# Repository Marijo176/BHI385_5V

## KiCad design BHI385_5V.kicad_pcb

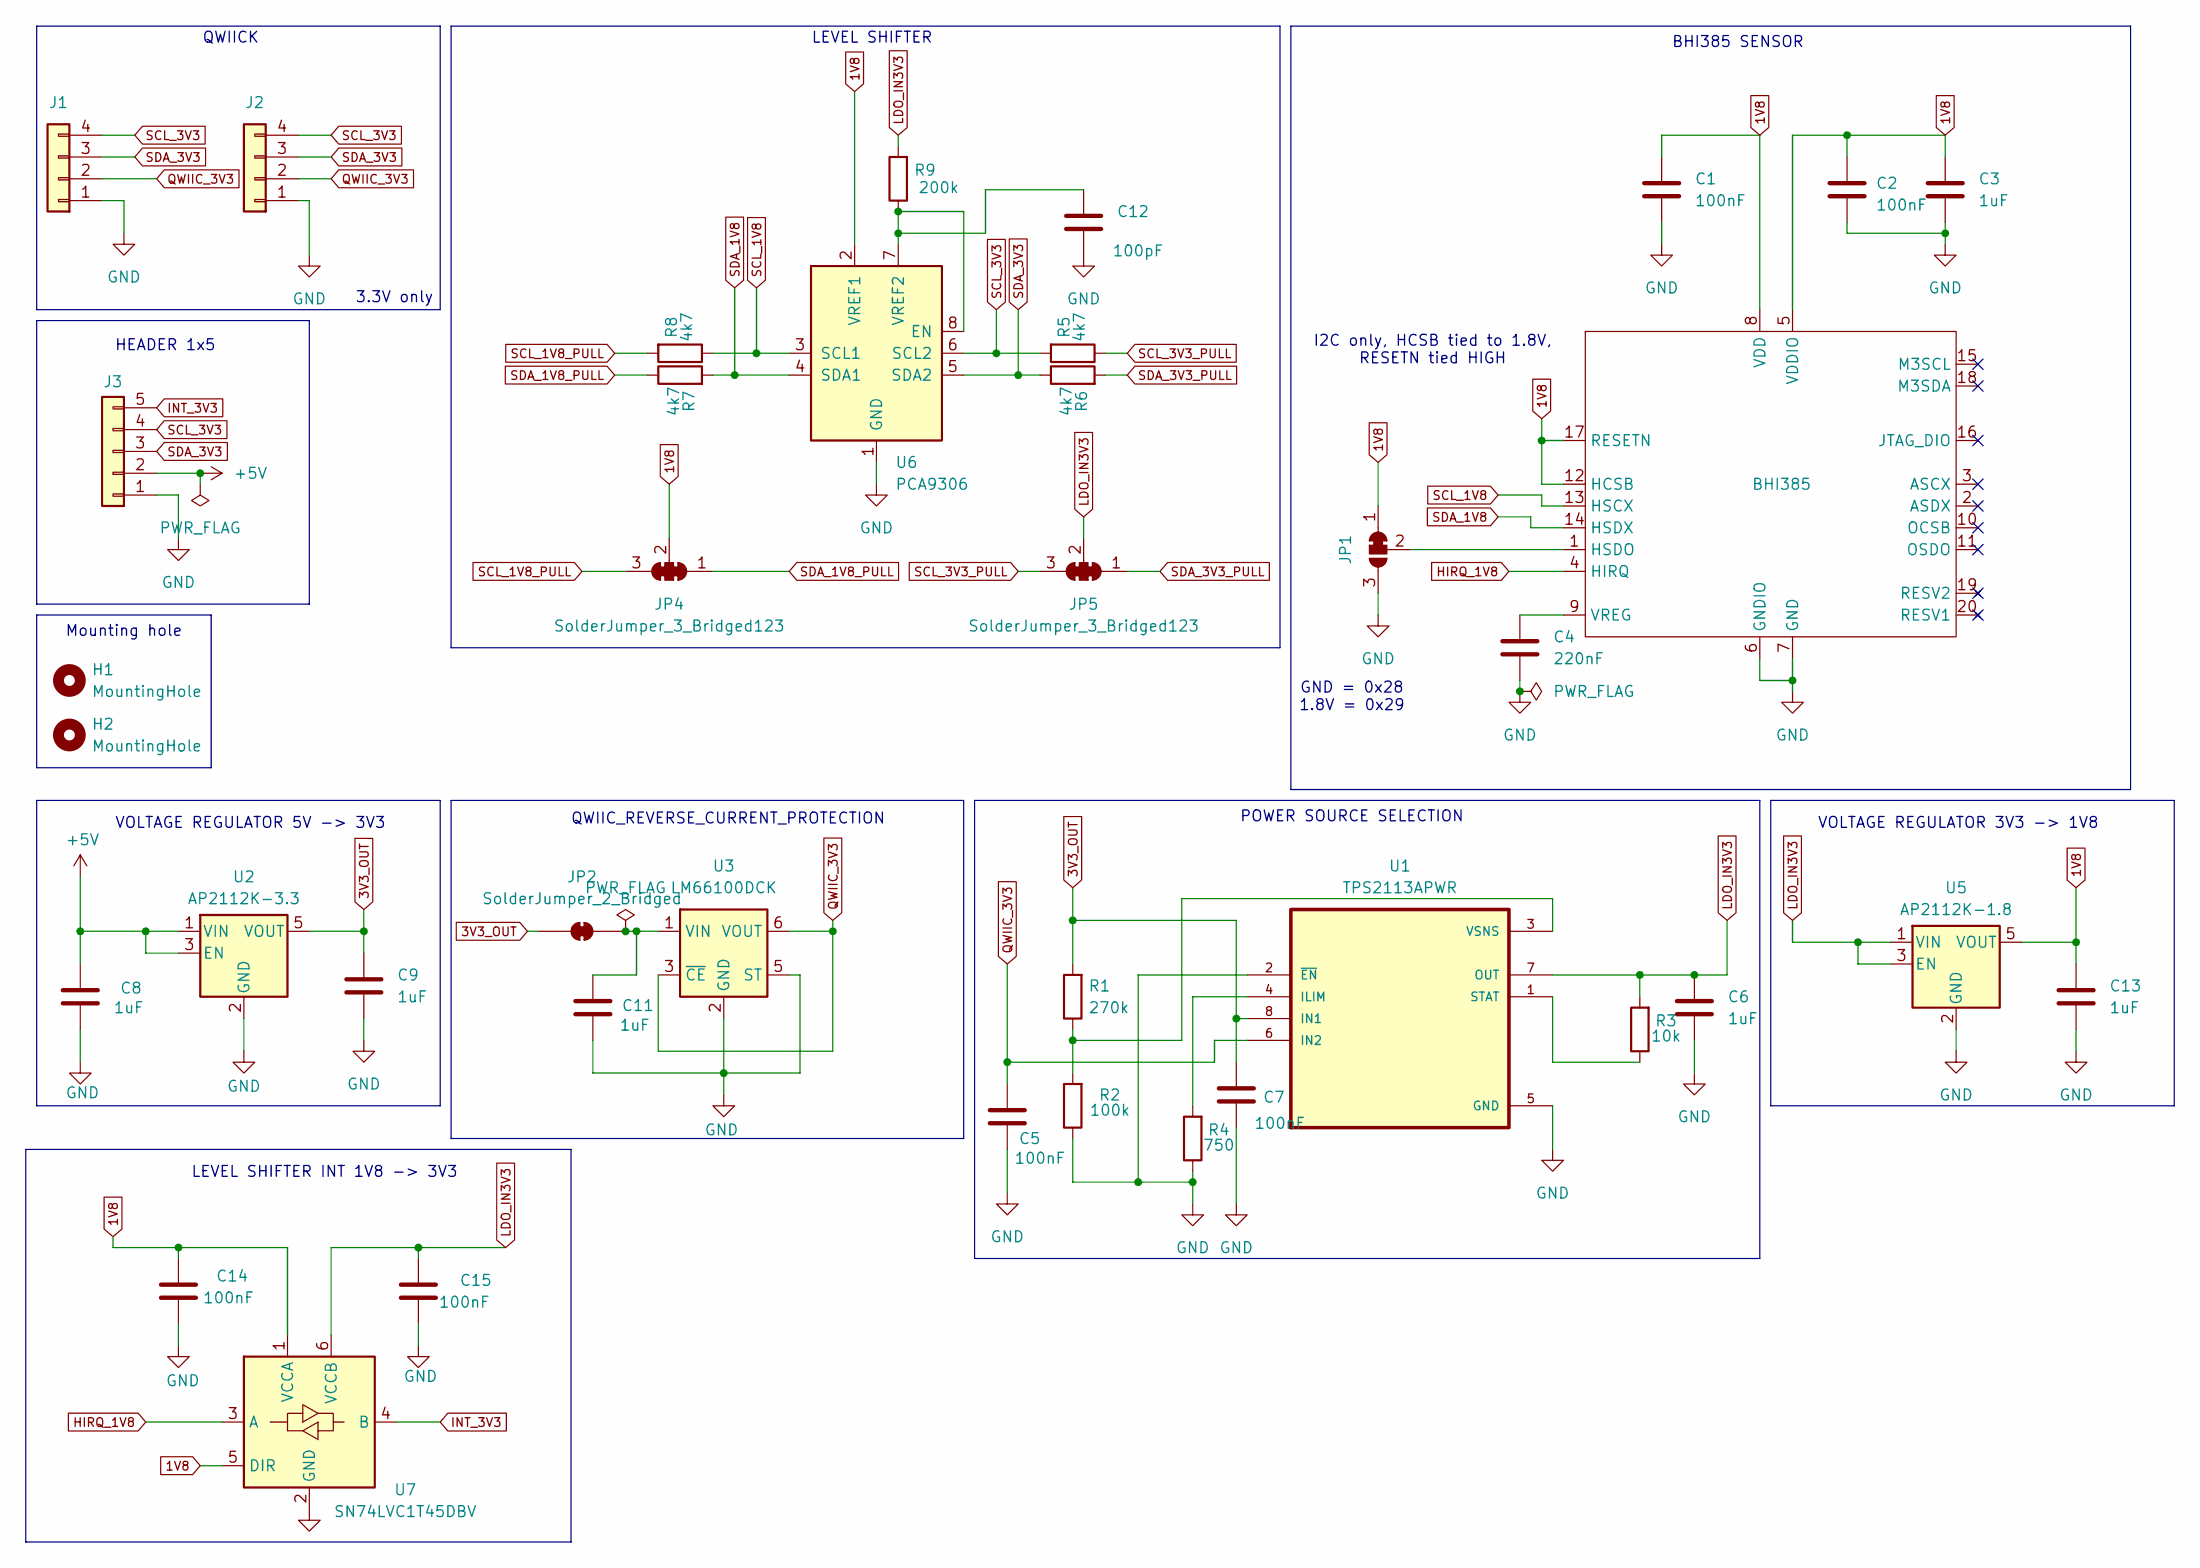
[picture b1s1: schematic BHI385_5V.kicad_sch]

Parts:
C1, C2, C5, C7, C14, C15: 100nF; C_0603_1608Metric
C3, C6, C8, C9, C11, C13: 1uF; C_0603_1608Metric
C4: 220nF; C_0603_1608Metric
C12: 100pF; C_0603_1608Metric
H1, H2: MountingHole; MountingHole_2.1mm
J1, J2: SM04B-SRSS-TB; JST_SH_SM04B-SRSS-TB_1x04-1MP_P1.00mm_Horizontal
J3: Conn_01x05; PinHeader_1x05_P2.54mm_Vertical
JP1: SolderJumper_3_Bridged12; SolderJumper-3_P1.3mm_Bridged12_Pad1.0x1.5mm
JP2: SolderJumper_2_Bridged; SolderJumper-2_P1.3mm_Bridged2Bar_Pad1.0x1.5mm
JP4, JP5: SolderJumper_3_Bridged123; SolderJumper-3_P1.3mm_Bridged2Bar123_Pad1.0x1.5mm
R1: 270k; R_0603_1608Metric
R2: 100k; R_0603_1608Metric
R3: 10k; R_0603_1608Metric
R4: 750; R_0603_1608Metric
R5, R6, R7, R8: 4k7; R_0603_1608Metric
R9: 200k; R_0603_1608Metric
U1: TPS2113APWR; TPS2113; MPN TPS2113APWR
U2: AP2112K-3.3; SOT-23-5
U3: LM66100DCK; SOT-363_SC-70-6
U4: BHI385; BHI385_LGA-20_2.5x3.0mm
U5: AP2112K-1.8; SOT-23-5
U6: PCA9306; VSSOP-8_2.3x2mm_P0.5mm
U7: SN74LVC1T45DBV; SOT-23-6

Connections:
1V8: C1.1, C2.1, C3.1, C13.1, C14.1, JP1.1 (A), JP4.2 (C), U4.5 (VDDIO), U4.8 (VDD), U4.12 (HCSB), U4.17 (RESETN), U5.5 (VOUT), U6.2 (VREF1), U7.1 (VCCA), U7.5 (DIR)
3V3_OUT: C7.1, C9.1, JP2.1 (A), R1.2, U1.8 (IN1), U2.5 (VOUT)
+5V: C8.1, J3.2, U2.1 (VIN), U2.3 (EN)
GND: C1.2, C2.2, C3.2, C4.2, C5.2, C6.2, C7.2, C8.2, C9.2, C11.2, C12.2, C13.2, C14.2, C15.2, J1.1, J2.1, J3.1, JP1.3 (B), R2.1, R4.1, U1.2 (~EN), U1.5 (GND), U2.2 (GND), U3.2 (GND), U3.5 (ST), U4.6 (GNDIO), U4.7 (GND), U5.2 (GND), U6.1 (GND), U7.2 (GND)
HIRQ_1V8: U4.4 (HIRQ), U7.3 (A)
INT_3V3: J3.5, U7.4 (B)
LDO_IN3V3: C6.1, C15.1, JP5.2 (C), R3.2, R9.2, U1.7 (OUT), U5.1 (VIN), U5.3 (EN), U7.6 (VCCB)
unnamed: JP1.2 (C), U4.1 (HSDO)
unnamed: C11.1, JP2.2 (B), U3.1 (VIN)
unnamed: R4.2, U1.4 (ILIM)
unnamed: R3.1, U1.1 (STAT)
unnamed: R1.1, R2.2, U1.3 (VSNS)
unnamed: C4.1, U4.9 (VREG)
unnamed: C12.1, R9.1, U6.7 (VREF2), U6.8 (EN)
QWIIC_3V3: C5.1, J1.2, J2.2, U1.6 (IN2), U3.3 (~CE), U3.6 (VOUT)
SCL_1V8: R8.1, U4.13 (HSCX), U6.3 (SCL1)
SCL_1V8_PULL: JP4.3 (B), R8.2
SCL_3V3: J1.4, J2.4, J3.4, R5.2, U6.6 (SCL2)
SCL_3V3_PULL: JP5.3 (B), R5.1
SDA_1V8: R7.2, U4.14 (HSDX), U6.4 (SDA1)
SDA_1V8_PULL: JP4.1 (A), R7.1
SDA_3V3: J1.3, J2.3, J3.3, R6.1, U6.5 (SDA2)
SDA_3V3_PULL: JP5.1 (A), R6.2

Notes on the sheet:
3.3V only
GND = 0x28 1.8V = 0x29
VOLTAGE REGULATOR 5V -> 3V3
HEADER 1x5
BHI385 SENSOR
QWIIC_REVERSE_CURRENT_PROTECTION
VOLTAGE REGULATOR 3V3 -> 1V8
Mounting hole
I2C only, HCSB tied to 1.8V, RESETN tied HIGH
POWER SOURCE SELECTION
QWIICK
LEVEL SHIFTER INT 1V8 -> 3V3
LEVEL SHIFTER

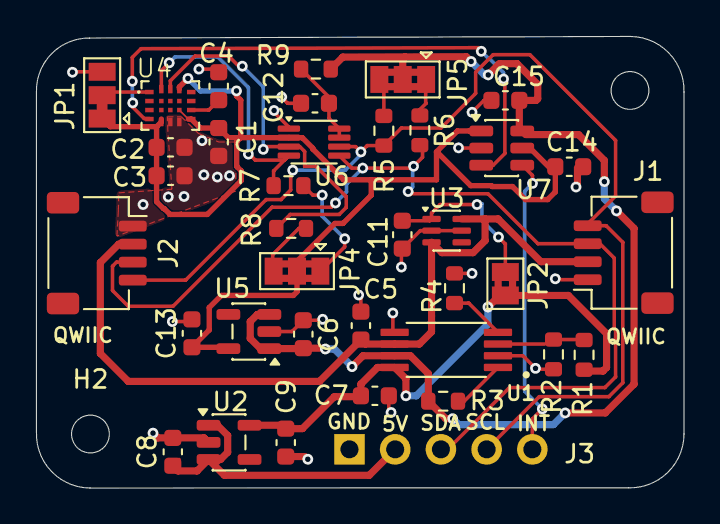
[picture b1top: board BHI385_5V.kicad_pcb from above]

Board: 2 copper layers, 36.0 x 25.1 mm, 39 parts (0 on the bottom side), 23 nets.
